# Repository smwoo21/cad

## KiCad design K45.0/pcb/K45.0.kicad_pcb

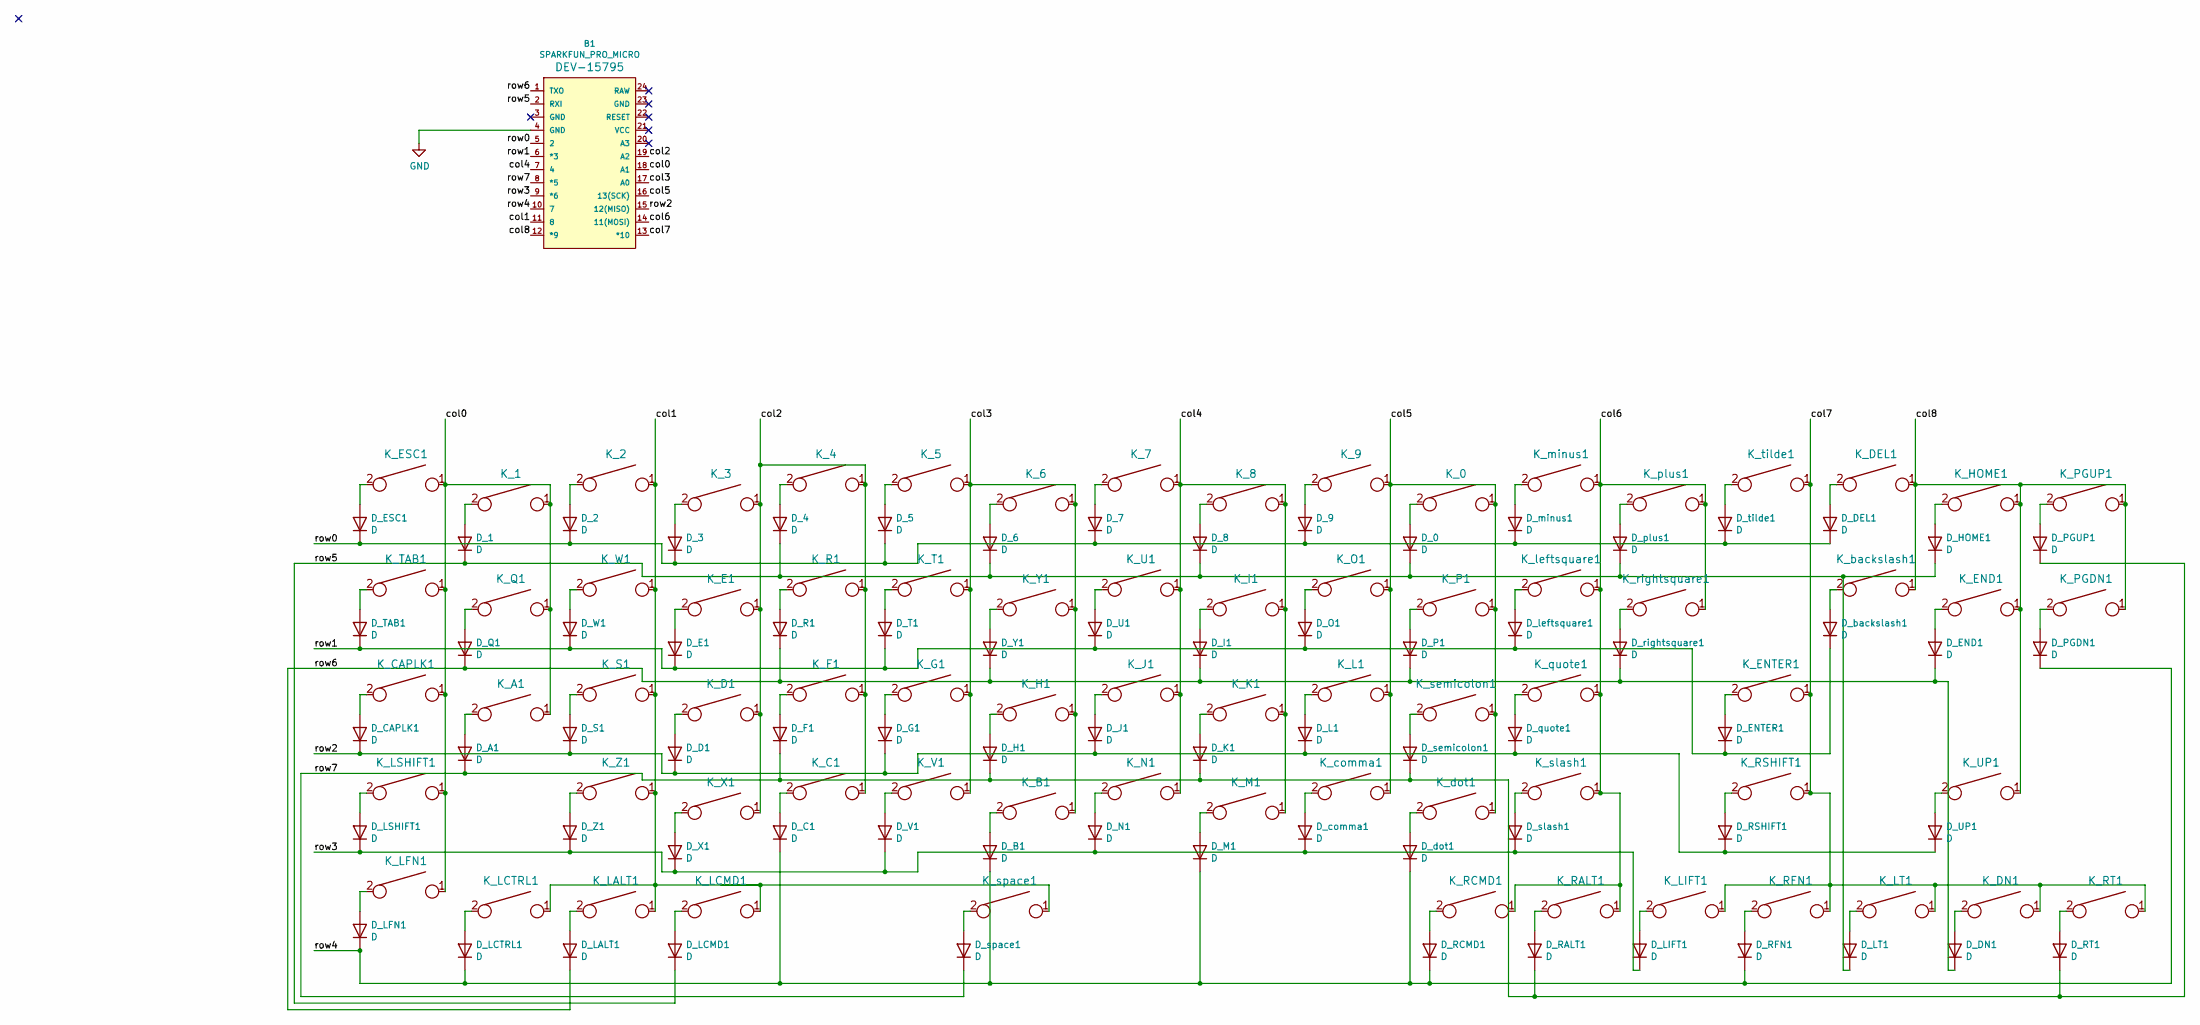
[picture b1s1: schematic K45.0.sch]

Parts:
B1: SPARKFUN_PRO_MICRO
D_0, D_1, D_2, D_3, D_4, D_5, D_6, D_7, D_8, D_9: D; D_SOD123_axial
D_A1: D; D_SOD123_axial
D_B1: D; D_SOD123_axial
D_C1: D; D_SOD123_axial
D_CAPLK1: D; D_SOD123_axial
D_D1: D; D_SOD123_axial
D_DEL1: D; D_SOD123_axial
D_DN1: D; D_SOD123_axial
D_E1: D; D_SOD123_axial
D_END1: D; D_SOD123_axial
D_ENTER1: D; D_SOD123_axial
D_ESC1: D; D_SOD123_axial
D_F1: D; D_SOD123_axial
D_G1: D; D_SOD123_axial
D_H1: D; D_SOD123_axial
D_HOME1: D; D_SOD123_axial
D_I1: D; D_SOD123_axial
D_J1: D; D_SOD123_axial
D_K1: D; D_SOD123_axial
D_L1: D; D_SOD123_axial
D_LALT1: D; D_SOD123_axial
D_LCMD1: D; D_SOD123_axial
D_LCTRL1: D; D_SOD123_axial
D_LFN1: D; D_SOD123_axial
D_LIFT1: D; D_SOD123_axial
D_LSHIFT1: D; D_SOD123_axial
D_LT1: D; D_SOD123_axial
D_M1: D; D_SOD123_axial
D_N1: D; D_SOD123_axial
D_O1: D; D_SOD123_axial
D_P1: D; D_SOD123_axial
D_PGDN1: D; D_SOD123_axial
D_PGUP1: D; D_SOD123_axial
D_Q1: D; D_SOD123_axial
D_R1: D; D_SOD123_axial
D_RALT1: D; D_SOD123_axial
D_RCMD1: D; D_SOD123_axial
D_RFN1: D; D_SOD123_axial
D_RSHIFT1: D; D_SOD123_axial
D_RT1: D; D_SOD123_axial
D_S1: D; D_SOD123_axial
D_T1: D; D_SOD123_axial
D_TAB1: D; D_SOD123_axial
D_U1: D; D_SOD123_axial
D_UP1: D; D_SOD123_axial
D_V1: D; D_SOD123_axial
D_W1: D; D_SOD123_axial
D_X1: D; D_SOD123_axial
D_Y1: D; D_SOD123_axial
D_Z1: D; D_SOD123_axial
D_backslash1: D; D_SOD123_axial
D_comma1: D; D_SOD123_axial
D_dot1: D; D_SOD123_axial
D_leftsquare1: D; D_SOD123_axial
D_minus1: D; D_SOD123_axial
D_plus1: D; D_SOD123_axial
D_quote1: D; D_SOD123_axial
D_rightsquare1: D; D_SOD123_axial
D_semicolon1: D; D_SOD123_axial
D_slash1: D; D_SOD123_axial
D_space1: D; D_SOD123_axial
D_tilde1: D; D_SOD123_axial
K_0, K_1, K_2, K_3, K_4, K_5, K_6, K_7, K_8, K_9: KEYSW; Mx_Alps_100
K_A1: KEYSW; Mx_Alps_100
K_B1: KEYSW; Mx_Alps_100
K_C1: KEYSW; Mx_Alps_100
K_CAPLK1: KEYSW; Mx_Alps_100
K_D1: KEYSW; Mx_Alps_100
K_DEL1: KEYSW; Mx_Alps_100
K_DN1: KEYSW; Mx_Alps_100
K_E1: KEYSW; Mx_Alps_100
K_END1: KEYSW; Mx_Alps_100
K_ENTER1: KEYSW; Mx_Alps_100
K_ESC1: KEYSW; Mx_Alps_100
K_F1: KEYSW; Mx_Alps_100
K_G1: KEYSW; Mx_Alps_100
K_H1: KEYSW; Mx_Alps_100
K_HOME1: KEYSW; Mx_Alps_100
K_I1: KEYSW; Mx_Alps_100
K_J1: KEYSW; Mx_Alps_100
K_K1: KEYSW; Mx_Alps_100
K_L1: KEYSW; Mx_Alps_100
K_LALT1: KEYSW; Mx_Alps_100
K_LCMD1: KEYSW; Mx_Alps_100
K_LCTRL1: KEYSW; Mx_Alps_100
K_LFN1: KEYSW; Mx_Alps_100
K_LIFT1: KEYSW; Mx_Alps_100
K_LSHIFT1: KEYSW; Mx_Alps_100
K_LT1: KEYSW; Mx_Alps_100
K_M1: KEYSW; Mx_Alps_100
K_N1: KEYSW; Mx_Alps_100
K_O1: KEYSW; Mx_Alps_100
K_P1: KEYSW; Mx_Alps_100
K_PGDN1: KEYSW; Mx_Alps_100
K_PGUP1: KEYSW; Mx_Alps_100
K_Q1: KEYSW; Mx_Alps_100
K_R1: KEYSW; Mx_Alps_100
K_RALT1: KEYSW; Mx_Alps_100
K_RCMD1: KEYSW; Mx_Alps_100
K_RFN1: KEYSW; Mx_Alps_100
K_RSHIFT1: KEYSW; Mx_Alps_100
K_RT1: KEYSW; Mx_Alps_100
K_S1: KEYSW; Mx_Alps_100
K_T1: KEYSW; Mx_Alps_100
K_TAB1: KEYSW; Mx_Alps_100
K_U1: KEYSW; Mx_Alps_100
K_UP1: KEYSW; Mx_Alps_100
K_V1: KEYSW; Mx_Alps_100
K_W1: KEYSW; Mx_Alps_100
K_X1: KEYSW; Mx_Alps_100
K_Y1: KEYSW; Mx_Alps_100
K_Z1: KEYSW; Mx_Alps_100
K_backslash1: KEYSW; Mx_Alps_100
K_comma1: KEYSW; Mx_Alps_100
K_dot1: KEYSW; Mx_Alps_100
K_leftsquare1: KEYSW; Mx_Alps_100
K_minus1: KEYSW; Mx_Alps_100
K_plus1: KEYSW; Mx_Alps_100
K_quote1: KEYSW; Mx_Alps_100
K_rightsquare1: KEYSW; Mx_Alps_100
K_semicolon1: KEYSW; Mx_Alps_100
K_slash1: KEYSW; Mx_Alps_100
K_space1: KEYSW; Mx_Alps_100
K_tilde1: KEYSW; Mx_Alps_100

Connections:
/col0: B1.18 (A1), K_1.1, K_A1.1, K_CAPLK1.1, K_ESC1.1, K_LFN1.1, K_LSHIFT1.1, K_Q1.1, K_TAB1.1
/col1: B1.11 (8), K_2.1, K_LALT1.1, K_LCMD1.1, K_LCTRL1.1, K_S1.1, K_W1.1, K_Z1.1, K_space1.1
/col2: B1.19 (A2), K_3.1, K_4.1, K_C1.1, K_D1.1, K_E1.1, K_F1.1, K_R1.1, K_X1.1
/col3: B1.17 (A0), K_5.1, K_6.1, K_B1.1, K_G1.1, K_H1.1, K_T1.1, K_V1.1, K_Y1.1
/col4: B1.7 (4), K_7.1, K_8.1, K_I1.1, K_J1.1, K_K1.1, K_M1.1, K_N1.1, K_U1.1
/col5: B1.16 (13(SCK)), K_0.1, K_9.1, K_L1.1, K_O1.1, K_P1.1, K_comma1.1, K_dot1.1, K_semicolon1.1
/col6: B1.14 (11(MOSI)), K_RALT1.1, K_RCMD1.1, K_leftsquare1.1, K_minus1.1, K_plus1.1, K_quote1.1, K_rightsquare1.1, K_slash1.1
/col7: B1.13 (*10), K_DN1.1, K_ENTER1.1, K_LIFT1.1, K_LT1.1, K_RFN1.1, K_RSHIFT1.1, K_RT1.1, K_tilde1.1
/col8: B1.12 (*9), K_DEL1.1, K_END1.1, K_HOME1.1, K_PGDN1.1, K_PGUP1.1, K_UP1.1, K_backslash1.1
/row0: B1.5 (2), D_2.1 (K), D_3.1 (K), D_5.1 (K), D_7.1 (K), D_9.1 (K), D_DEL1.1 (K), D_ESC1.1 (K), D_minus1.1 (K), D_tilde1.1 (K)
/row1: B1.6 (*3), D_E1.1 (K), D_ENTER1.1 (K), D_O1.1 (K), D_T1.1 (K), D_TAB1.1 (K), D_U1.1 (K), D_W1.1 (K), D_backslash1.1 (K), D_leftsquare1.1 (K)
/row2: B1.15 (12(MISO)), D_CAPLK1.1 (K), D_D1.1 (K), D_G1.1 (K), D_J1.1 (K), D_L1.1 (K), D_RSHIFT1.1 (K), D_S1.1 (K), D_UP1.1 (K), D_quote1.1 (K)
/row3: B1.9 (*6), D_LIFT1.1 (K), D_LSHIFT1.1 (K), D_N1.1 (K), D_V1.1 (K), D_X1.1 (K), D_Z1.1 (K), D_comma1.1 (K), D_slash1.1 (K)
/row4: B1.10 (7), D_B1.1 (K), D_C1.1 (K), D_LCTRL1.1 (K), D_LFN1.1 (K), D_M1.1 (K), D_PGDN1.1 (K), D_RCMD1.1 (K), D_RFN1.1 (K), D_dot1.1 (K)
/row5: B1.2 (RXI), D_0.1 (K), D_1.1 (K), D_4.1 (K), D_6.1 (K), D_8.1 (K), D_HOME1.1 (K), D_LCMD1.1 (K), D_LT1.1 (K), D_plus1.1 (K)
/row6: B1.1 (TXO), D_DN1.1 (K), D_END1.1 (K), D_I1.1 (K), D_LALT1.1 (K), D_P1.1 (K), D_Q1.1 (K), D_R1.1 (K), D_Y1.1 (K), D_rightsquare1.1 (K)
/row7: B1.8 (*5), D_A1.1 (K), D_F1.1 (K), D_H1.1 (K), D_K1.1 (K), D_PGUP1.1 (K), D_RALT1.1 (K), D_RT1.1 (K), D_semicolon1.1 (K), D_space1.1 (K)
GND: B1.4 (GND)
unnamed: D_0.2 (A), K_0.2
unnamed: D_1.2 (A), K_1.2
unnamed: D_2.2 (A), K_2.2
unnamed: D_3.2 (A), K_3.2
unnamed: D_4.2 (A), K_4.2
unnamed: D_5.2 (A), K_5.2
unnamed: D_6.2 (A), K_6.2
unnamed: D_7.2 (A), K_7.2
unnamed: D_8.2 (A), K_8.2
unnamed: D_9.2 (A), K_9.2
unnamed: D_A1.2 (A), K_A1.2
unnamed: D_B1.2 (A), K_B1.2
unnamed: D_C1.2 (A), K_C1.2
unnamed: D_CAPLK1.2 (A), K_CAPLK1.2
unnamed: D_D1.2 (A), K_D1.2
unnamed: D_DEL1.2 (A), K_DEL1.2
unnamed: D_DN1.2 (A), K_DN1.2
unnamed: D_E1.2 (A), K_E1.2
unnamed: D_END1.2 (A), K_END1.2
unnamed: D_ENTER1.2 (A), K_ENTER1.2
unnamed: D_ESC1.2 (A), K_ESC1.2
unnamed: D_F1.2 (A), K_F1.2
unnamed: D_G1.2 (A), K_G1.2
unnamed: D_H1.2 (A), K_H1.2
unnamed: D_HOME1.2 (A), K_HOME1.2
unnamed: D_I1.2 (A), K_I1.2
unnamed: D_J1.2 (A), K_J1.2
unnamed: D_K1.2 (A), K_K1.2
unnamed: D_L1.2 (A), K_L1.2
unnamed: D_LALT1.2 (A), K_LALT1.2
unnamed: D_LCMD1.2 (A), K_LCMD1.2
unnamed: D_LCTRL1.2 (A), K_LCTRL1.2
unnamed: D_LFN1.2 (A), K_LFN1.2
unnamed: D_LIFT1.2 (A), K_LIFT1.2
unnamed: D_LSHIFT1.2 (A), K_LSHIFT1.2
unnamed: D_LT1.2 (A), K_LT1.2
unnamed: D_M1.2 (A), K_M1.2
unnamed: D_N1.2 (A), K_N1.2
unnamed: D_O1.2 (A), K_O1.2
unnamed: D_P1.2 (A), K_P1.2
unnamed: D_PGDN1.2 (A), K_PGDN1.2
unnamed: D_PGUP1.2 (A), K_PGUP1.2
unnamed: D_Q1.2 (A), K_Q1.2
unnamed: D_R1.2 (A), K_R1.2
unnamed: D_RALT1.2 (A), K_RALT1.2
unnamed: D_RCMD1.2 (A), K_RCMD1.2
unnamed: D_RFN1.2 (A), K_RFN1.2
unnamed: D_RSHIFT1.2 (A), K_RSHIFT1.2
unnamed: D_RT1.2 (A), K_RT1.2
unnamed: D_S1.2 (A), K_S1.2
unnamed: D_T1.2 (A), K_T1.2
unnamed: D_TAB1.2 (A), K_TAB1.2
unnamed: D_U1.2 (A), K_U1.2
unnamed: D_UP1.2 (A), K_UP1.2
unnamed: D_V1.2 (A), K_V1.2
unnamed: D_W1.2 (A), K_W1.2
unnamed: D_X1.2 (A), K_X1.2
unnamed: D_Y1.2 (A), K_Y1.2
unnamed: D_Z1.2 (A), K_Z1.2
unnamed: D_backslash1.2 (A), K_backslash1.2
unnamed: D_comma1.2 (A), K_comma1.2
unnamed: D_dot1.2 (A), K_dot1.2
unnamed: D_leftsquare1.2 (A), K_leftsquare1.2
unnamed: D_minus1.2 (A), K_minus1.2
unnamed: D_plus1.2 (A), K_plus1.2
unnamed: D_quote1.2 (A), K_quote1.2
unnamed: D_rightsquare1.2 (A), K_rightsquare1.2
unnamed: D_semicolon1.2 (A), K_semicolon1.2
unnamed: D_slash1.2 (A), K_slash1.2
unnamed: D_space1.2 (A), K_space1.2
unnamed: D_tilde1.2 (A), K_tilde1.2

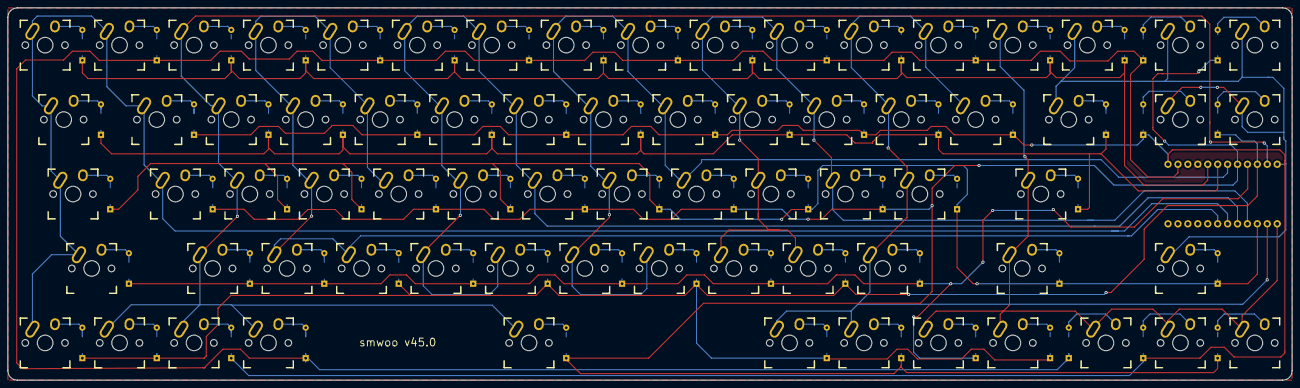
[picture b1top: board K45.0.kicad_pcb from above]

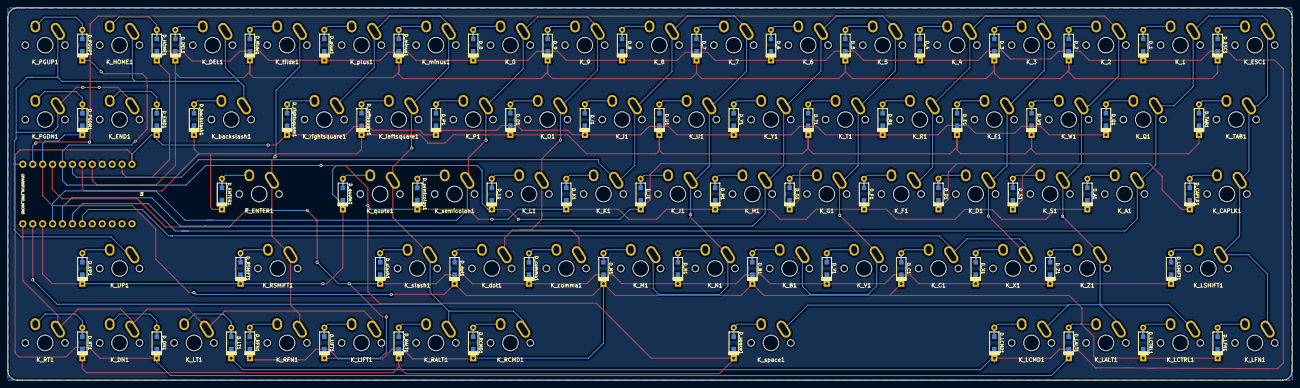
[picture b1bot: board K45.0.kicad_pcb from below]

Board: 2 copper layers, 328.6 x 95.2 mm, 143 parts (72 on the bottom side), 88 nets.

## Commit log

2020-08-15 v45.0 keyboard design initial checkin
2021-03-10 added case design
